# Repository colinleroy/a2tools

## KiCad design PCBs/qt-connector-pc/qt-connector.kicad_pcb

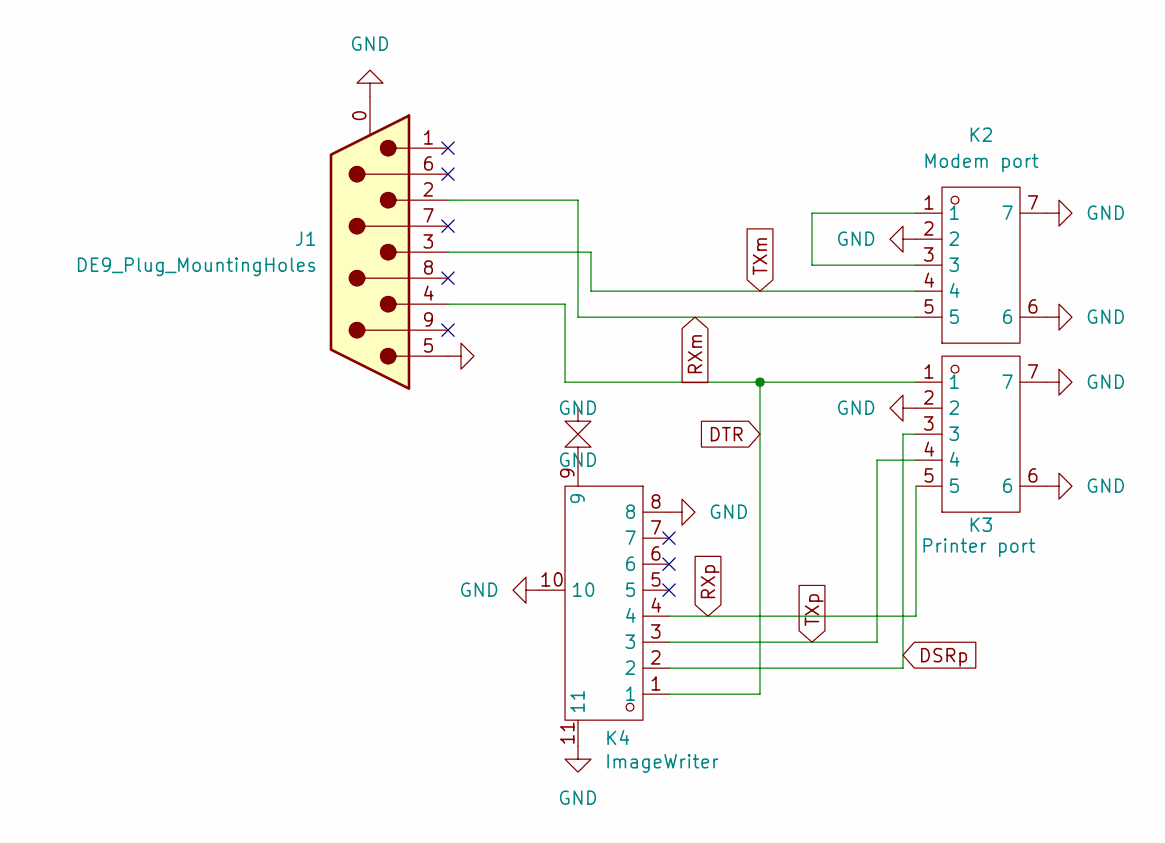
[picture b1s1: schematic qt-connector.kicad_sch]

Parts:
J1: DE9_Plug_MountingHoles; DSUB-9_Male_Horizontal_P2.77x2.84mm_EdgePinOffset7.70mm_Hou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; LCSC C19077344
K2: Modem port; CONN-TH_DIN-504-M10; Manufacturer Part DIN-504; LCSC Part Name DIN插座
K3: Printer port; CONN-TH_DIN-504-M10; Manufacturer Part DIN-504; LCSC Part Name DIN插座
K4: ImageWriter; MINI-DIN8; Manufacturer Part DIN-802; LCSC Part Name DIN插座

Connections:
DSRp: K3.3, K4.2
DTR: J1.4, K3.1, K4.1
GND: J1.0 (PAD), J1.5, K2.2, K2.6, K2.7, K3.2, K3.6, K3.7, K4.8, K4.9, K4.10, K4.11
unnamed: K2.1, K2.3
RXm: J1.2, K2.5
RXp: K3.5, K4.4
TXm: J1.3, K2.4
TXp: K3.4, K4.3

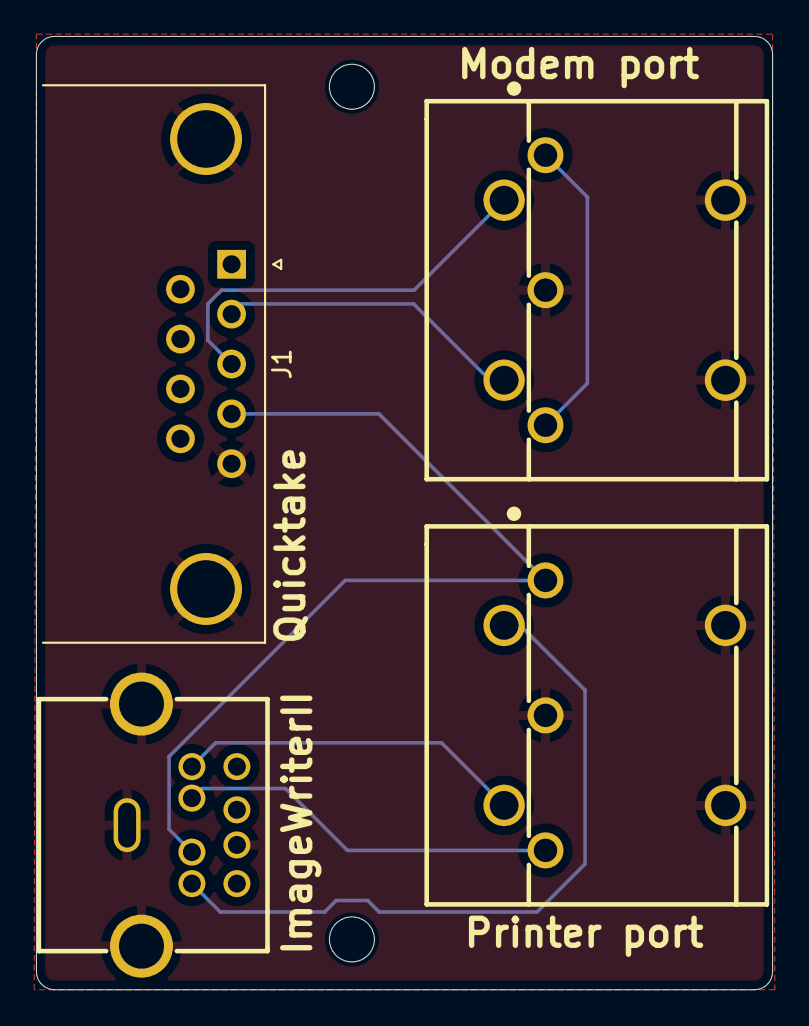
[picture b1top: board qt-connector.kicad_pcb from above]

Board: 2 copper layers, 40.9 x 53.0 mm, 4 parts (0 on the bottom side), 8 nets.
